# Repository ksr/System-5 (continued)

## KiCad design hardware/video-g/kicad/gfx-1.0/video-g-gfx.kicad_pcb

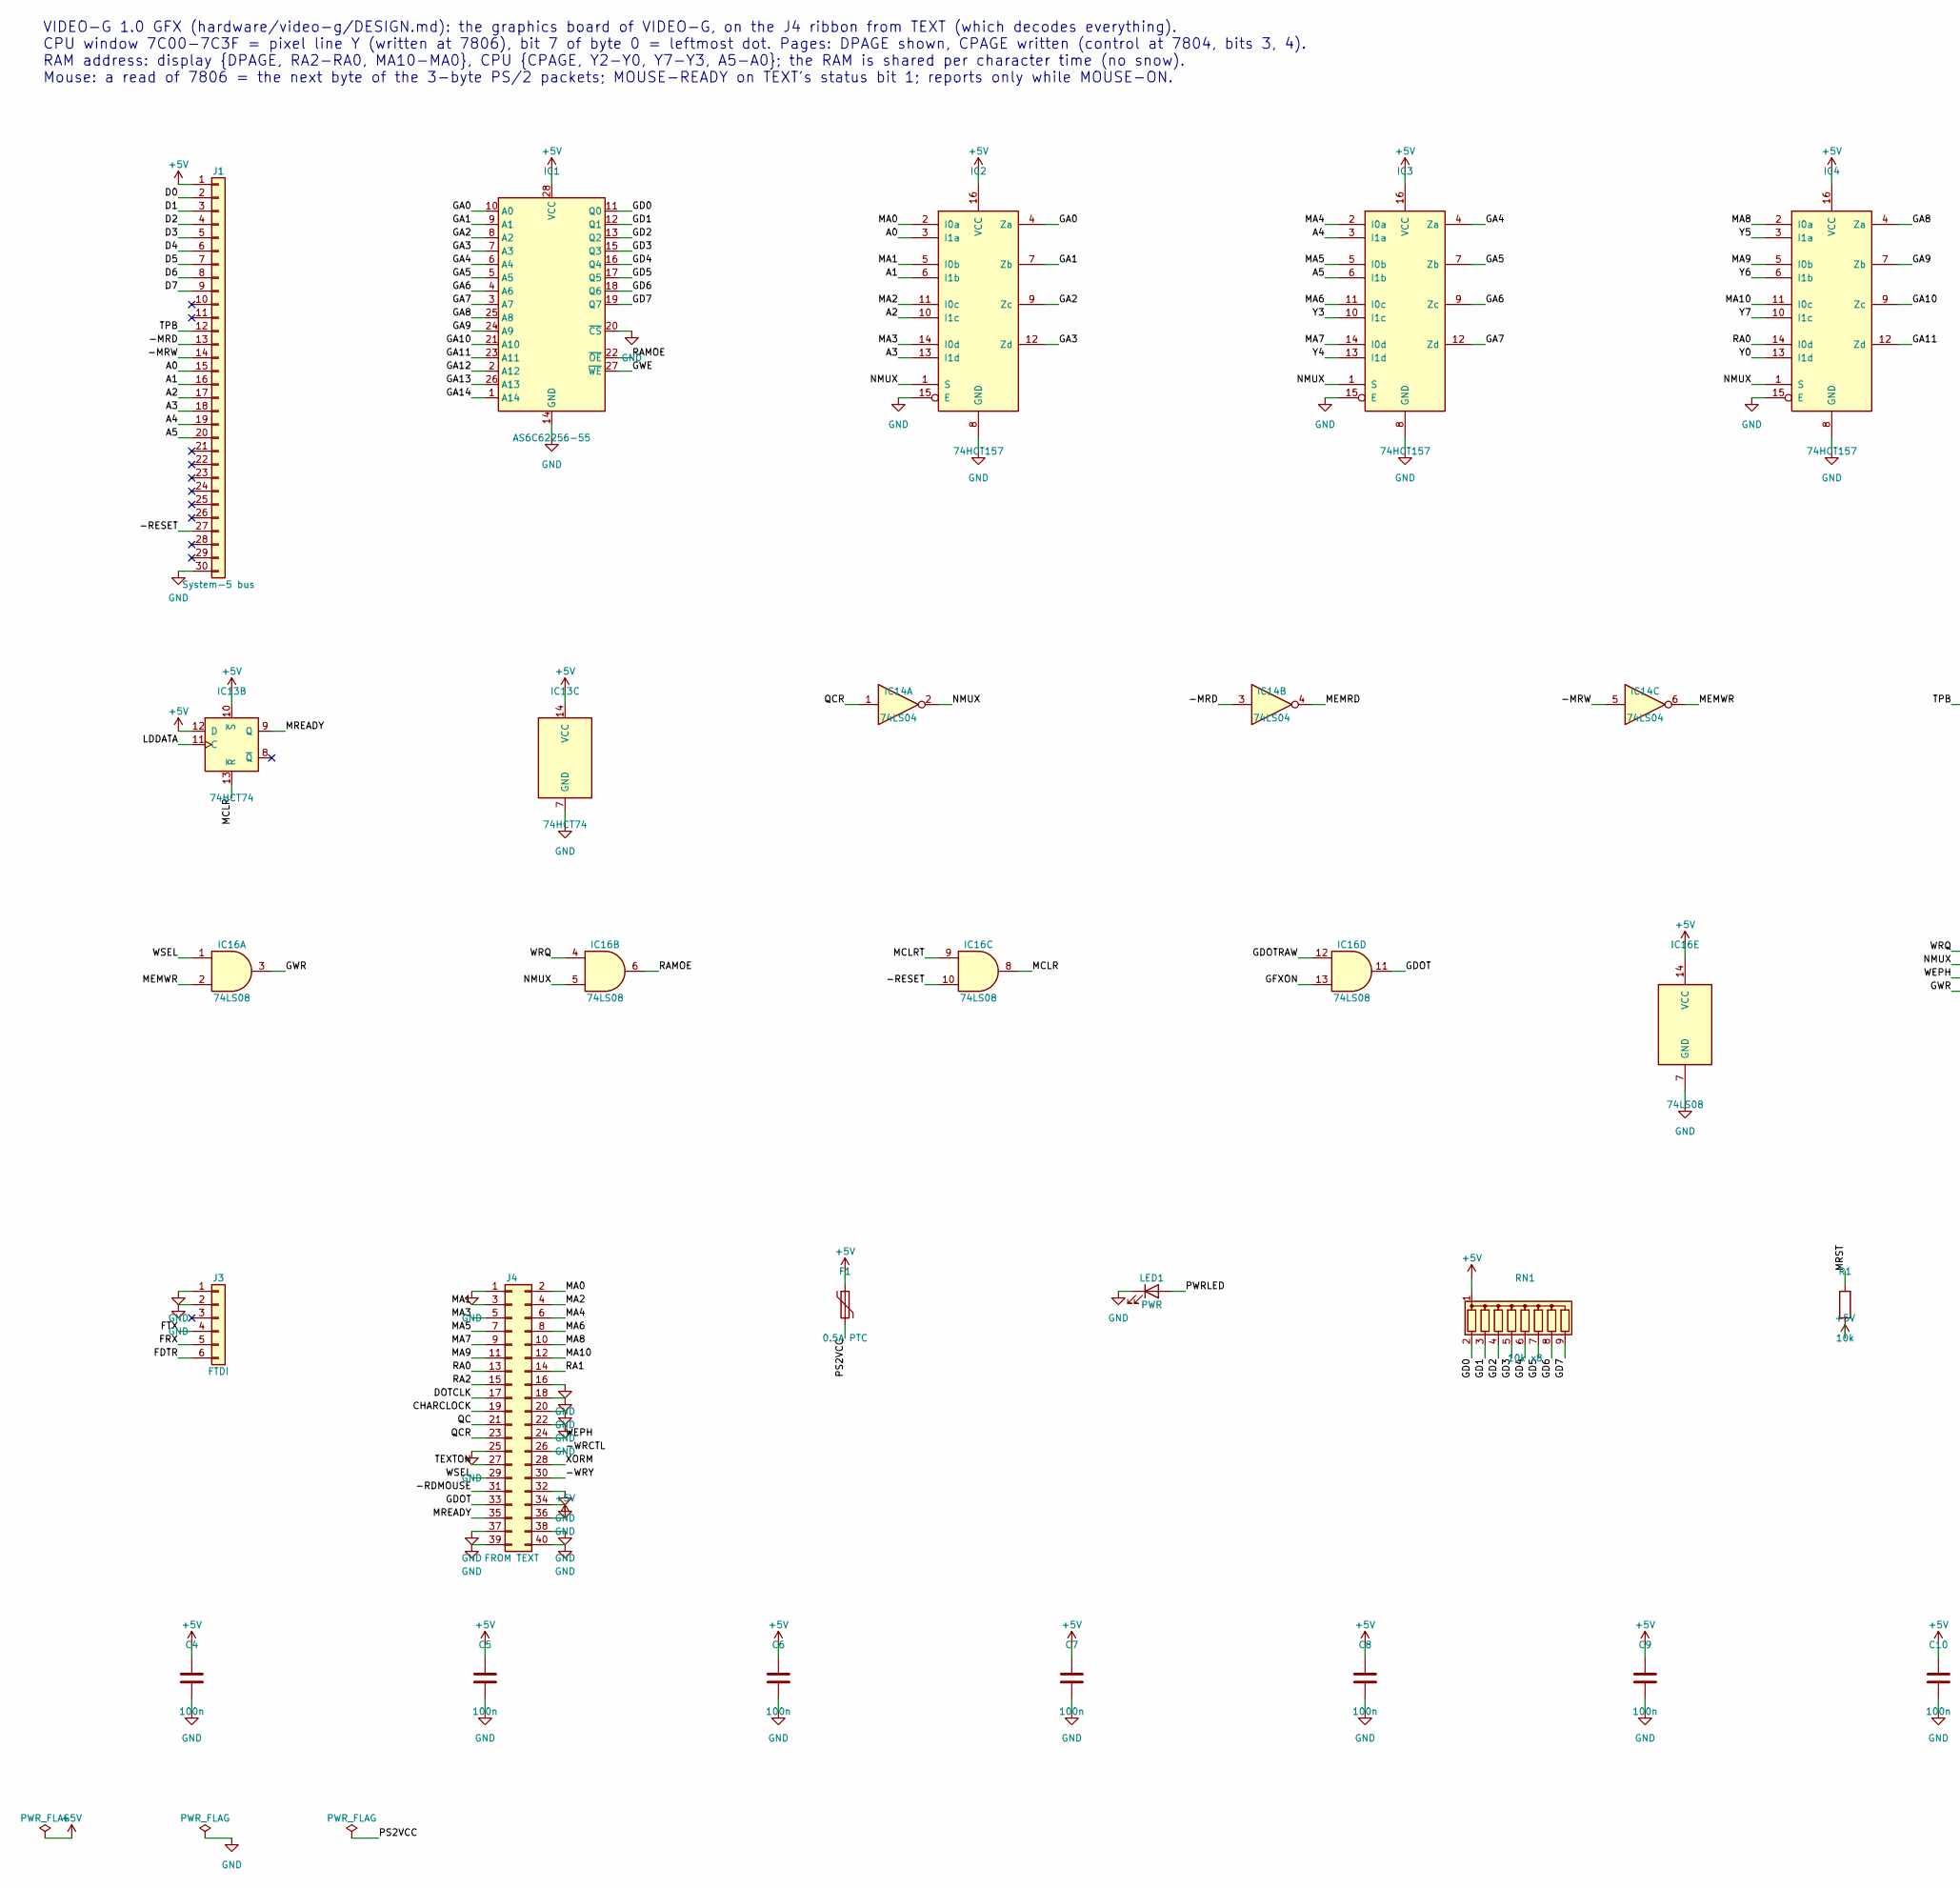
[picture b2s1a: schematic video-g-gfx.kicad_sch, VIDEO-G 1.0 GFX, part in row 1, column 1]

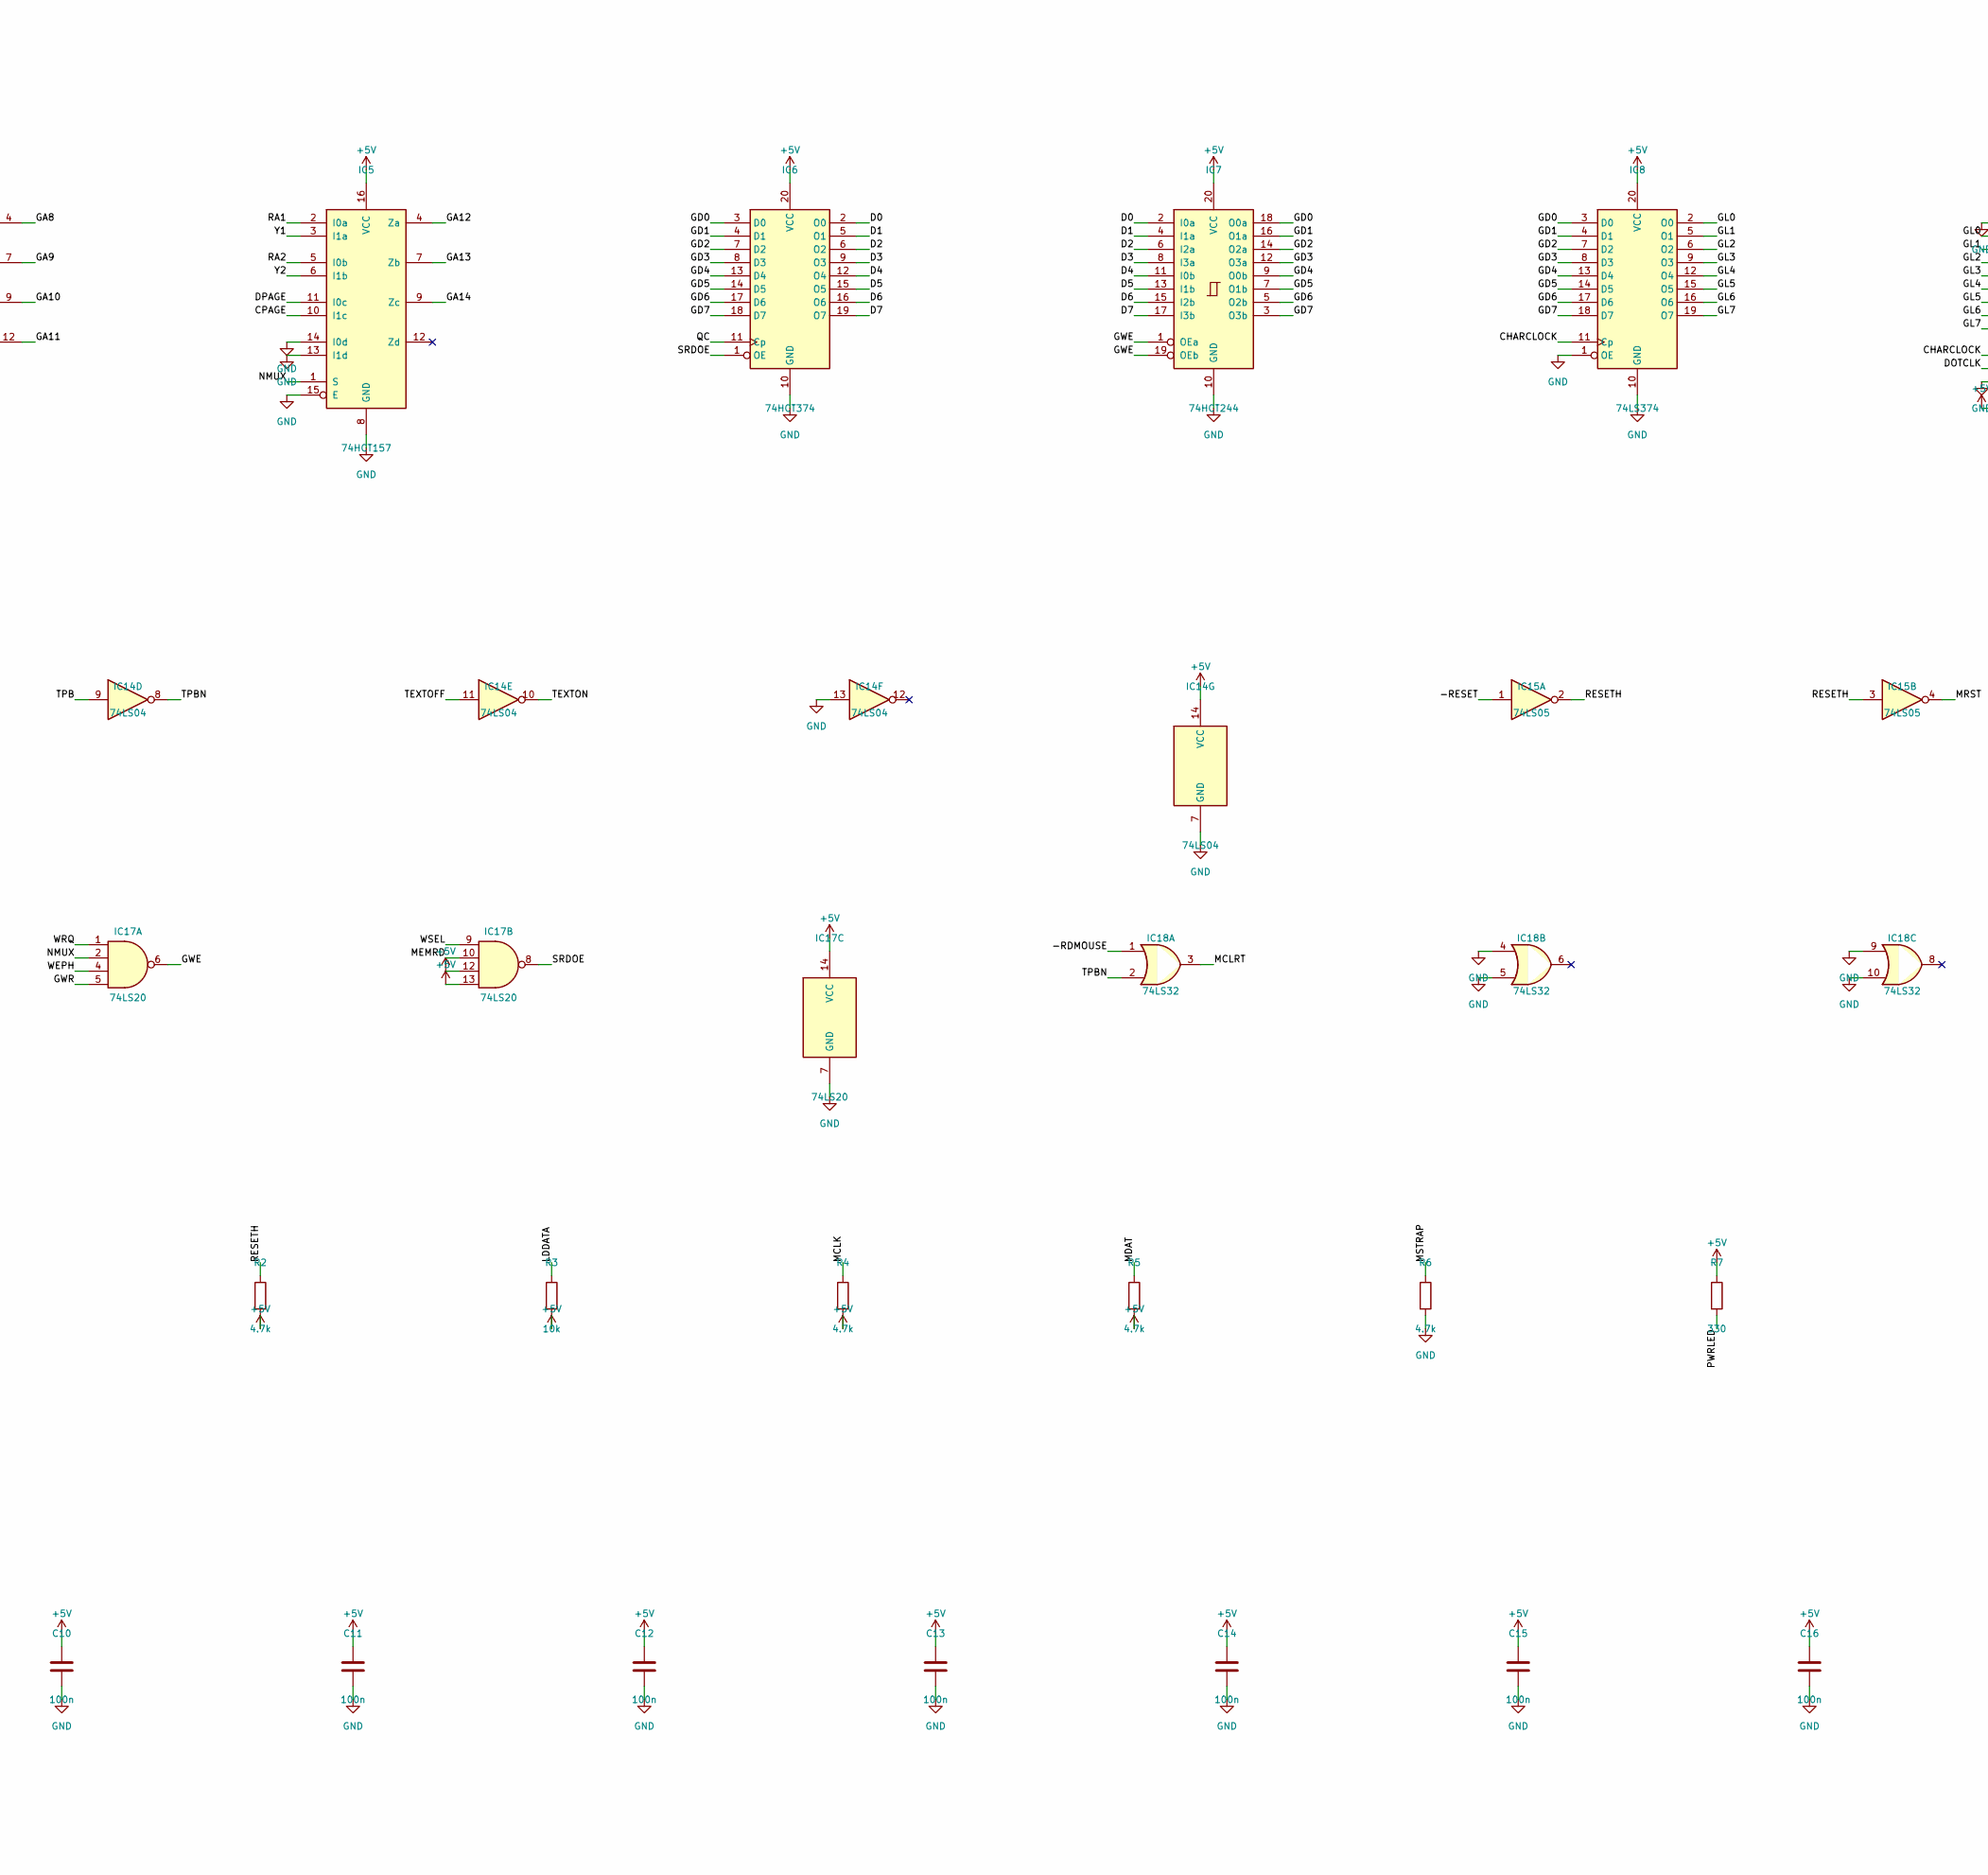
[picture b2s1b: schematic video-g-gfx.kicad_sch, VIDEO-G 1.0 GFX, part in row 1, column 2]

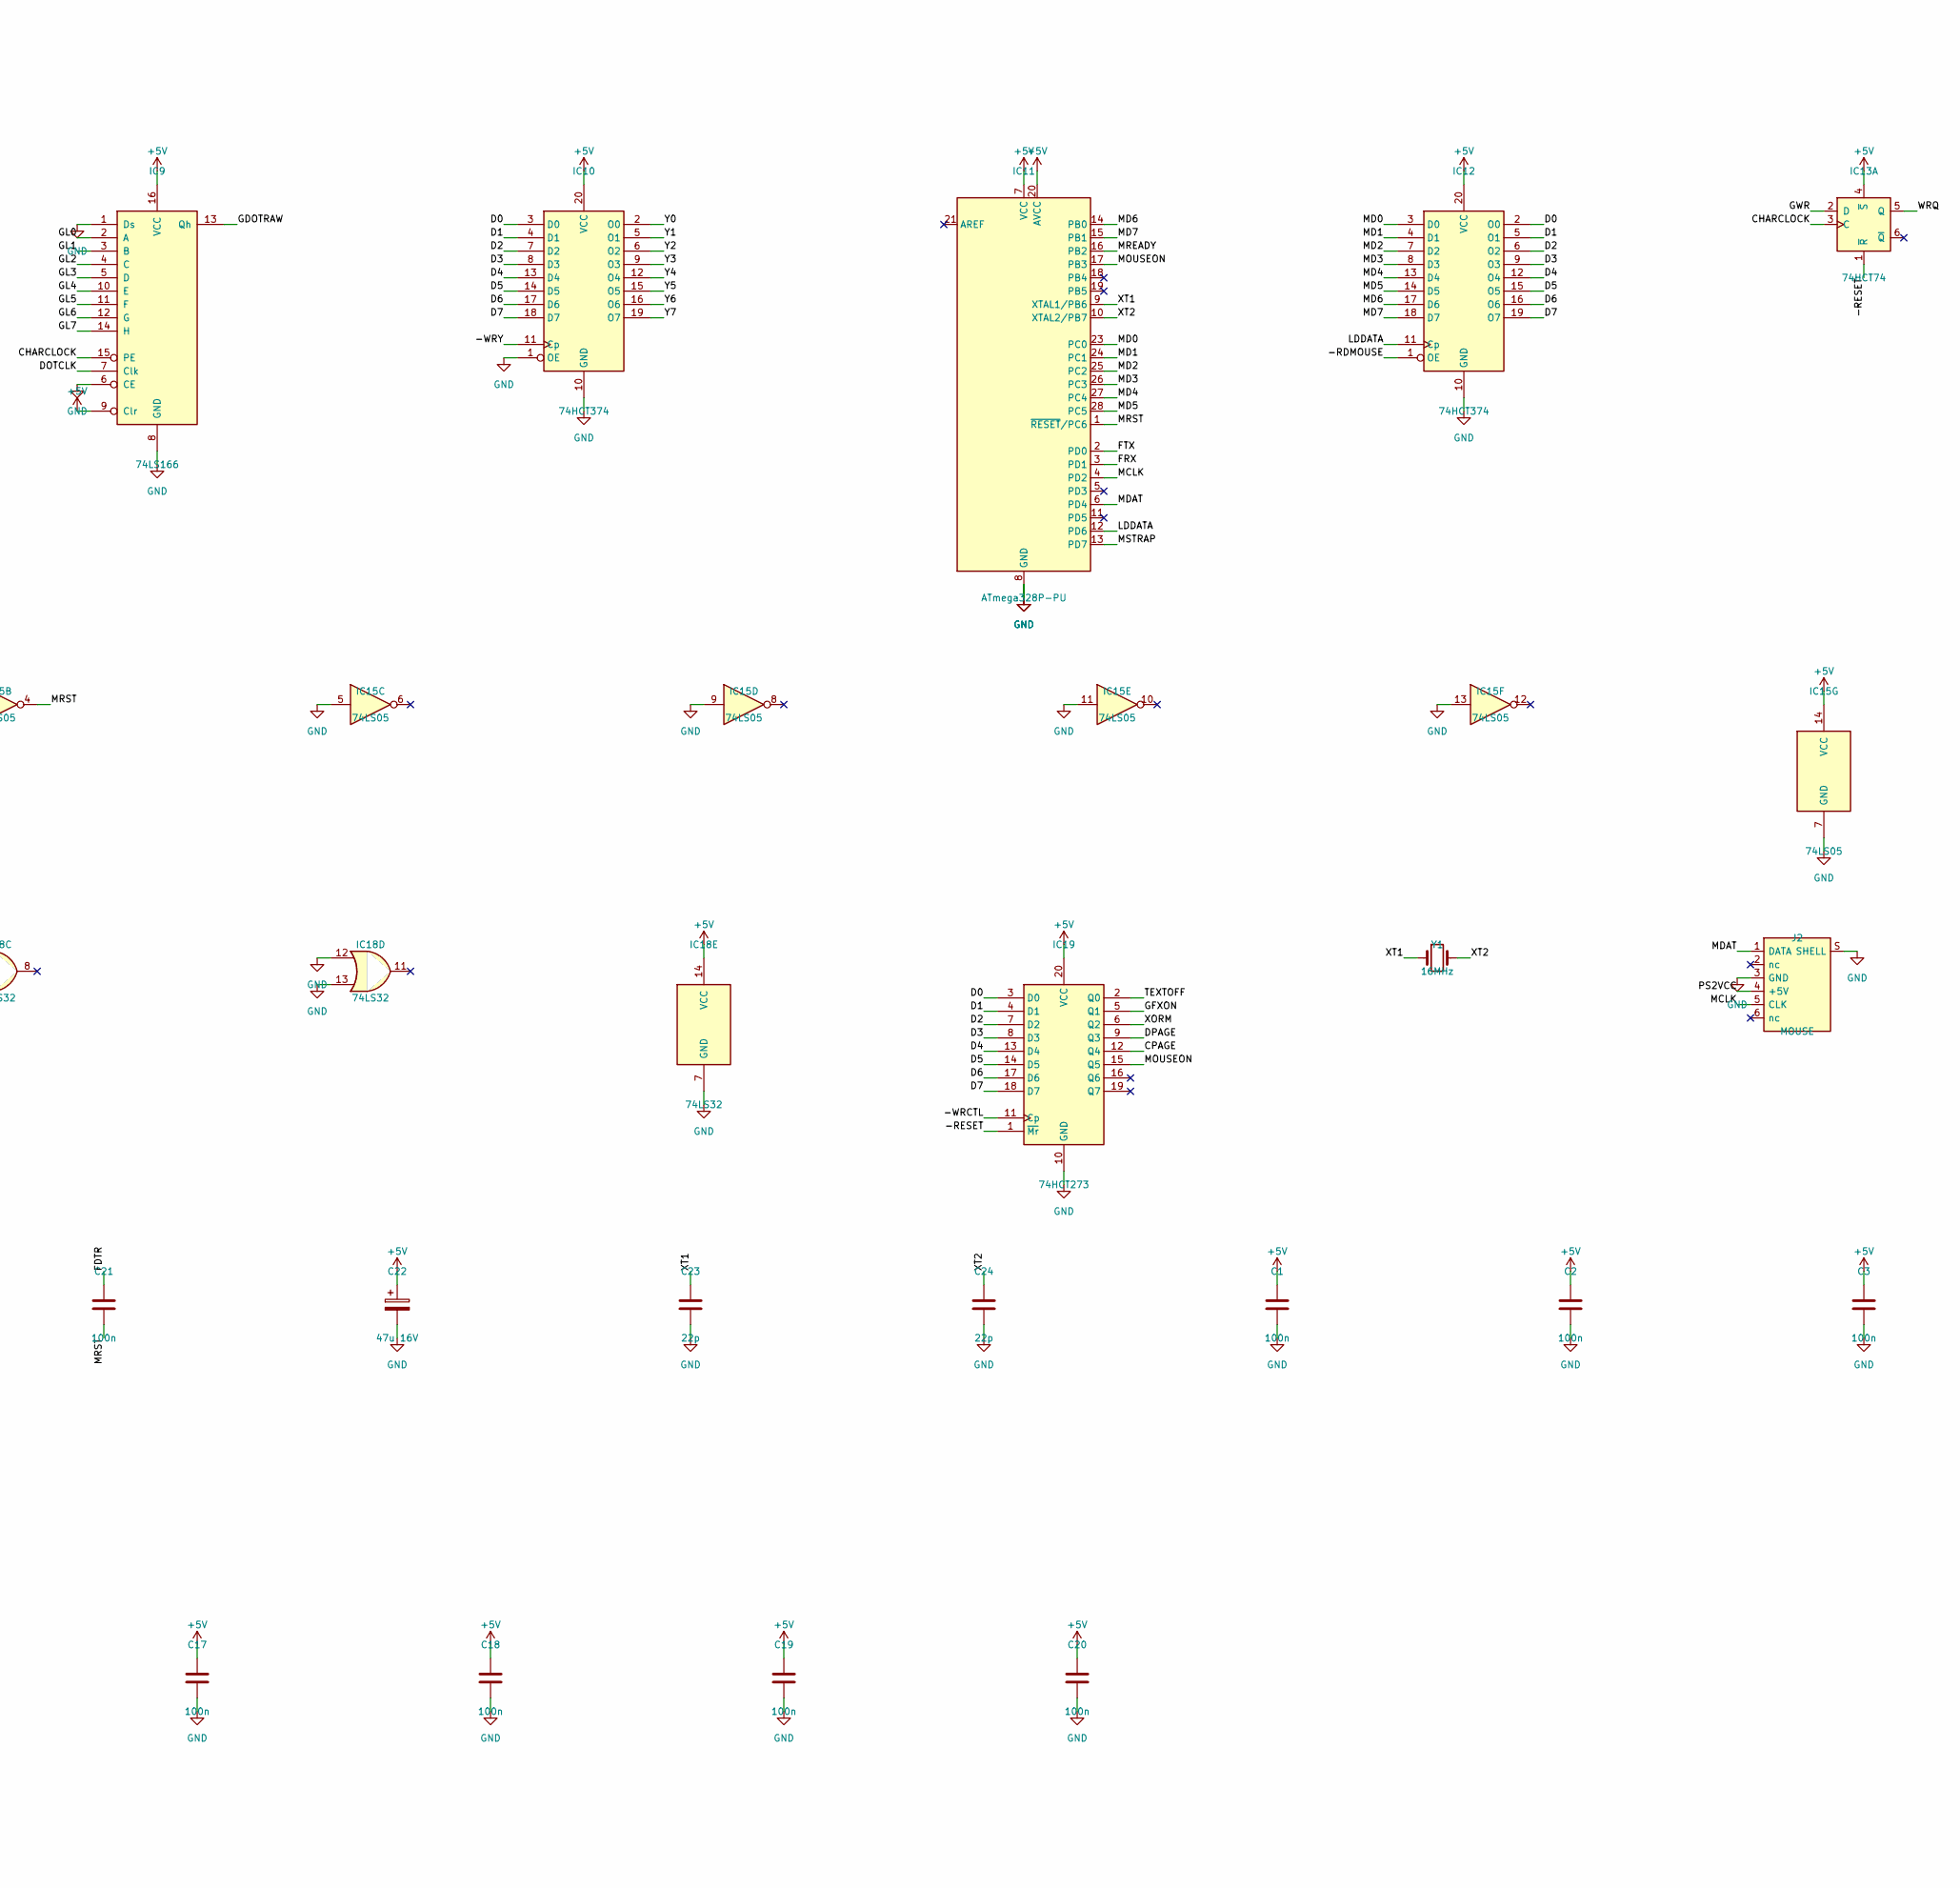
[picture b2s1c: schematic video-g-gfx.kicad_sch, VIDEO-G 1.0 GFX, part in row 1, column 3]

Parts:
C1, C2, C3, C4, C5, C6, C7, C8, C9, C10, C11, C12, C13, C14, C15, C16, C17, C18, C19, C20, C21: 100n; C025-050X050
C22: 47u 16V; CP_Radial_D6.3mm_P2.50mm
C23, C24: 22p; C025-050X050
F1: 0.5A PTC; Fuse_Bourns_MF-RHT050
IC1: AS6C62256-55; DIP-28_W15.24mm_Socket
IC2, IC3, IC4, IC5: 74HCT157; DIP-16_W7.62mm_Socket
IC6, IC10, IC12: 74HCT374; DIP-20_W7.62mm_Socket
IC7: 74HCT244; DIP-20_W7.62mm_Socket
IC8: 74LS374; DIP-20_W7.62mm_Socket
IC9: 74LS166; DIP-16_W7.62mm_Socket
IC11: ATmega328P-PU; DIP-28_W7.62mm_Socket
IC13: 74HCT74; DIP-14_W7.62mm_Socket
IC14: 74LS04; DIP-14_W7.62mm_Socket
IC15: 74LS05; DIP-14_W7.62mm_Socket
IC16: 74LS08; DIP-14_W7.62mm_Socket
IC17: 74LS20; DIP-14_W7.62mm_Socket
IC18: 74LS32; DIP-14_W7.62mm_Socket
IC19: 74HCT273; DIP-20_W7.62mm_Socket
J1: System-5 bus; C30
J2: MOUSE; MiniDIN6_MD-60SM
J3: FTDI; PinHeader_1x06_P2.54mm_Vertical
J4: FROM TEXT; IDC-Header_2x20_P2.54mm_Vertical
LED1: PWR; LED_D5.0mm
R1, R3: 10k; R_Axial_DIN0207_L6.3mm_D2.5mm_P2.54mm_Vertical
R2, R4, R5, R6: 4.7k; R_Axial_DIN0207_L6.3mm_D2.5mm_P2.54mm_Vertical
R7: 330; R_Axial_DIN0207_L6.3mm_D2.5mm_P2.54mm_Vertical
RN1: 10k x8; R_Array_SIP9
Y1: 16MHz; Crystal_HC49-U_Vertical

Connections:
+5V: C1.1, C2.1, C3.1, C4.1, C5.1, C6.1, C7.1, C8.1, C9.1, C10.1, C11.1, C12.1, C13.1, C14.1, C15.1, C16.1, C17.1, C18.1, C19.1, C20.1, C22.1, F1.1, IC1.28 (VCC), IC2.16 (VCC), IC3.16 (VCC), IC4.16 (VCC), IC5.16 (VCC), IC6.20 (VCC), IC7.20 (VCC), IC8.20 (VCC), IC9.9 (Clr), IC9.16 (VCC), IC10.20 (VCC), IC11.7 (VCC), IC11.20 (AVCC), IC12.20 (VCC), IC13.4 (~S), IC13.10 (~S), IC13.12 (D), IC13.14 (VCC), IC14.14 (VCC), IC15.14 (VCC), IC16.14 (VCC), IC17.12, IC17.13, IC17.14 (VCC), IC18.14 (VCC), IC19.20 (VCC), J1.1, J4.36, R1.2, R2.2, R3.2, R4.2, R5.2, R7.1, RN1.1 (common)
/-MRD: IC14.3, J1.13
/-MRW: IC14.5, J1.14
/-RDMOUSE: IC12.1 (OE), IC18.1, J4.31
/-RESET: IC13.1 (~R), IC15.1, IC16.10, IC19.1 (~Mr), J1.27
/-WRCTL: IC19.11 (Cp), J4.26
/-WRY: IC10.11 (Cp), J4.30
/A0: IC2.3 (I1a), J1.15
/A1: IC2.6 (I1b), J1.16
/A2: IC2.10 (I1c), J1.17
/A3: IC2.13 (I1d), J1.18
/A4: IC3.3 (I1a), J1.19
/A5: IC3.6 (I1b), J1.20
/CHARCLOCK: IC8.11 (Cp), IC9.15 (PE), IC13.3 (C), J4.19
/CPAGE: IC5.10 (I1c), IC19.12 (Q4)
/D0: IC6.2 (O0), IC7.2 (I0a), IC10.3 (D0), IC12.2 (O0), IC19.3 (D0), J1.2
/D1: IC6.5 (O1), IC7.4 (I1a), IC10.4 (D1), IC12.5 (O1), IC19.4 (D1), J1.3
/D2: IC6.6 (O2), IC7.6 (I2a), IC10.7 (D2), IC12.6 (O2), IC19.7 (D2), J1.4
/D3: IC6.9 (O3), IC7.8 (I3a), IC10.8 (D3), IC12.9 (O3), IC19.8 (D3), J1.5
/D4: IC6.12 (O4), IC7.11 (I0b), IC10.13 (D4), IC12.12 (O4), IC19.13 (D4), J1.6
/D5: IC6.15 (O5), IC7.13 (I1b), IC10.14 (D5), IC12.15 (O5), IC19.14 (D5), J1.7
/D6: IC6.16 (O6), IC7.15 (I2b), IC10.17 (D6), IC12.16 (O6), IC19.17 (D6), J1.8
/D7: IC6.19 (O7), IC7.17 (I3b), IC10.18 (D7), IC12.19 (O7), IC19.18 (D7), J1.9
/DOTCLK: IC9.7 (Clk), J4.17
/DPAGE: IC5.11 (I0c), IC19.9 (Q3)
/FDTR: C21.1, J3.6
/FRX: IC11.3 (PD1), J3.5
/FTX: IC11.2 (PD0), J3.4
/GA0: IC1.10 (A0), IC2.4 (Za)
/GA1: IC1.9 (A1), IC2.7 (Zb)
/GA2: IC1.8 (A2), IC2.9 (Zc)
/GA3: IC1.7 (A3), IC2.12 (Zd)
/GA4: IC1.6 (A4), IC3.4 (Za)
/GA5: IC1.5 (A5), IC3.7 (Zb)
/GA6: IC1.4 (A6), IC3.9 (Zc)
/GA7: IC1.3 (A7), IC3.12 (Zd)
/GA8: IC1.25 (A8), IC4.4 (Za)
/GA9: IC1.24 (A9), IC4.7 (Zb)
/GA10: IC1.21 (A10), IC4.9 (Zc)
/GA11: IC1.23 (A11), IC4.12 (Zd)
/GA12: IC1.2 (A12), IC5.4 (Za)
/GA13: IC1.26 (A13), IC5.7 (Zb)
/GA14: IC1.1 (A14), IC5.9 (Zc)
/GD0: IC1.11 (Q0), IC6.3 (D0), IC7.18 (O0a), IC8.3 (D0), RN1.2 (R1)
/GD1: IC1.12 (Q1), IC6.4 (D1), IC7.16 (O1a), IC8.4 (D1), RN1.3 (R2)
/GD2: IC1.13 (Q2), IC6.7 (D2), IC7.14 (O2a), IC8.7 (D2), RN1.4 (R3)
/GD3: IC1.15 (Q3), IC6.8 (D3), IC7.12 (O3a), IC8.8 (D3), RN1.5 (R4)
/GD4: IC1.16 (Q4), IC6.13 (D4), IC7.9 (O0b), IC8.13 (D4), RN1.6 (R5)
/GD5: IC1.17 (Q5), IC6.14 (D5), IC7.7 (O1b), IC8.14 (D5), RN1.7 (R6)
/GD6: IC1.18 (Q6), IC6.17 (D6), IC7.5 (O2b), IC8.17 (D6), RN1.8 (R7)
/GD7: IC1.19 (Q7), IC6.18 (D7), IC7.3 (O3b), IC8.18 (D7), RN1.9 (R8)
/GDOT: IC16.11, J4.33
/GDOTRAW: IC9.13 (Qh), IC16.12
/GFXON: IC16.13, IC19.5 (Q1)
/GL0: IC8.2 (O0), IC9.2 (A)
/GL1: IC8.5 (O1), IC9.3 (B)
/GL2: IC8.6 (O2), IC9.4 (C)
/GL3: IC8.9 (O3), IC9.5 (D)
/GL4: IC8.12 (O4), IC9.10 (E)
/GL5: IC8.15 (O5), IC9.11 (F)
/GL6: IC8.16 (O6), IC9.12 (G)
/GL7: IC8.19 (O7), IC9.14 (H)
/GWE: IC1.27 (~WE), IC7.1 (OEa), IC7.19 (OEb), IC17.6
/GWR: IC13.2 (D), IC16.3, IC17.5
/LDDATA: IC11.12 (PD6), IC12.11 (Cp), IC13.11 (C), R3.1
/MA0: IC2.2 (I0a), J4.2
/MA1: IC2.5 (I0b), J4.3
/MA2: IC2.11 (I0c), J4.4
/MA3: IC2.14 (I0d), J4.5
/MA4: IC3.2 (I0a), J4.6
/MA5: IC3.5 (I0b), J4.7
/MA6: IC3.11 (I0c), J4.8
/MA7: IC3.14 (I0d), J4.9
/MA8: IC4.2 (I0a), J4.10
/MA9: IC4.5 (I0b), J4.11
/MA10: IC4.11 (I0c), J4.12
/MCLK: IC11.4 (PD2), J2.5 (CLK), R4.1
/MCLR: IC13.13 (~R), IC16.8
/MCLRT: IC16.9, IC18.3
/MD0: IC11.23 (PC0), IC12.3 (D0)
/MD1: IC11.24 (PC1), IC12.4 (D1)
/MD2: IC11.25 (PC2), IC12.7 (D2)
/MD3: IC11.26 (PC3), IC12.8 (D3)
/MD4: IC11.27 (PC4), IC12.13 (D4)
/MD5: IC11.28 (PC5), IC12.14 (D5)
/MD6: IC11.14 (PB0), IC12.17 (D6)
/MD7: IC11.15 (PB1), IC12.18 (D7)
/MDAT: IC11.6 (PD4), J2.1 (DATA), R5.1
/MEMRD: IC14.4, IC17.10
/MEMWR: IC14.6, IC16.2
/MOUSEON: IC11.17 (PB3), IC19.15 (Q5)
/MREADY: IC11.16 (PB2), IC13.9 (Q), J4.35
/MRST: C21.2, IC11.1 (~RESET/PC6), IC15.4, R1.1
/MSTRAP: IC11.13 (PD7), R6.1
/NMUX: IC2.1 (S), IC3.1 (S), IC4.1 (S), IC5.1 (S), IC14.2, IC16.5, IC17.2
/PS2VCC: F1.2, J2.4 (+5V)
/PWRLED: LED1.2 (A), R7.2
/QC: IC6.11 (Cp), J4.21
/QCR: IC14.1, J4.23
/RA0: IC4.14 (I0d), J4.13
/RA1: IC5.2 (I0a), J4.14
/RA2: IC5.5 (I0b), J4.15
/RAMOE: IC1.22 (~OE), IC16.6
/RESETH: IC15.2, IC15.3, R2.1
/SRDOE: IC6.1 (OE), IC17.8
/TEXTOFF: IC14.11, IC19.2 (Q0)
/TEXTON: IC14.10, J4.27
/TPB: IC14.9, J1.12
/TPBN: IC14.8, IC18.2
/WEPH: IC17.4, J4.24
/WRQ: IC13.5 (Q), IC16.4, IC17.1
/WSEL: IC16.1, IC17.9, J4.29
/XORM: IC19.6 (Q2), J4.28
/XT1: C23.1, IC11.9 (XTAL1/PB6), Y1.1
/XT2: C24.1, IC11.10 (XTAL2/PB7), Y1.2
/Y0: IC4.13 (I1d), IC10.2 (O0)
/Y1: IC5.3 (I1a), IC10.5 (O1)
/Y2: IC5.6 (I1b), IC10.6 (O2)
/Y3: IC3.10 (I1c), IC10.9 (O3)
/Y4: IC3.13 (I1d), IC10.12 (O4)
/Y5: IC4.3 (I1a), IC10.15 (O5)
/Y6: IC4.6 (I1b), IC10.16 (O6)
/Y7: IC4.10 (I1c), IC10.19 (O7)
GND: C1.2, C2.2, C3.2, C4.2, C5.2, C6.2, C7.2, C8.2, C9.2, C10.2, C11.2, C12.2, C13.2, C14.2, C15.2, C16.2, C17.2, C18.2, C19.2, C20.2, C22.2, C23.2, C24.2, IC1.14 (GND), IC1.20 (~CS), IC2.8 (GND), IC2.15 (E), IC3.8 (GND), IC3.15 (E), IC4.8 (GND), IC4.15 (E), IC5.8 (GND), IC5.13 (I1d), IC5.14 (I0d), IC5.15 (E), IC6.10 (GND), IC7.10 (GND), IC8.1 (OE), IC8.10 (GND), IC9.1 (Ds), IC9.6 (CE), IC9.8 (GND), IC10.1 (OE), IC10.10 (GND), IC11.8 (GND), IC11.22 (GND), IC12.10 (GND), IC13.7 (GND), IC14.7 (GND), IC14.13, IC15.5, IC15.7 (GND), IC15.9, IC15.11, IC15.13, IC16.7 (GND), IC17.7 (GND), IC18.4, IC18.5, IC18.7 (GND), IC18.9, IC18.10, IC18.12, IC18.13, IC19.10 (GND), J1.30, J2.3 (GND), J2.S (SHELL), J3.1, J3.2, J4.1, J4.16, J4.18, J4.20, J4.22, J4.25, J4.32, J4.34, J4.37, J4.38, J4.39, J4.40, LED1.1 (K), R6.2

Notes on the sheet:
VIDEO-G 1.0 GFX (hardware/video-g/DESIGN.md): the graphics board of VIDEO-G, on the J4 ribbon from TEXT (which decodes everything).
CPU window 7C00-7C3F = pixel line Y (written at 7806), bit 7 of byte 0 = leftmost dot. Pages: DPAGE shown, CPAGE written (control at 7804, bits 3, 4).
RAM address: display {DPAGE, RA2-RA0, MA10-MA0}, CPU {CPAGE, Y2-Y0, Y7-Y3, A5-A0}; the RAM is shared per character time (no snow).
Mouse: a read of 7806 = the next byte of the 3-byte PS/2 packets; MOUSE-READY on TEXT's status bit 1; reports only while MOUSE-ON.

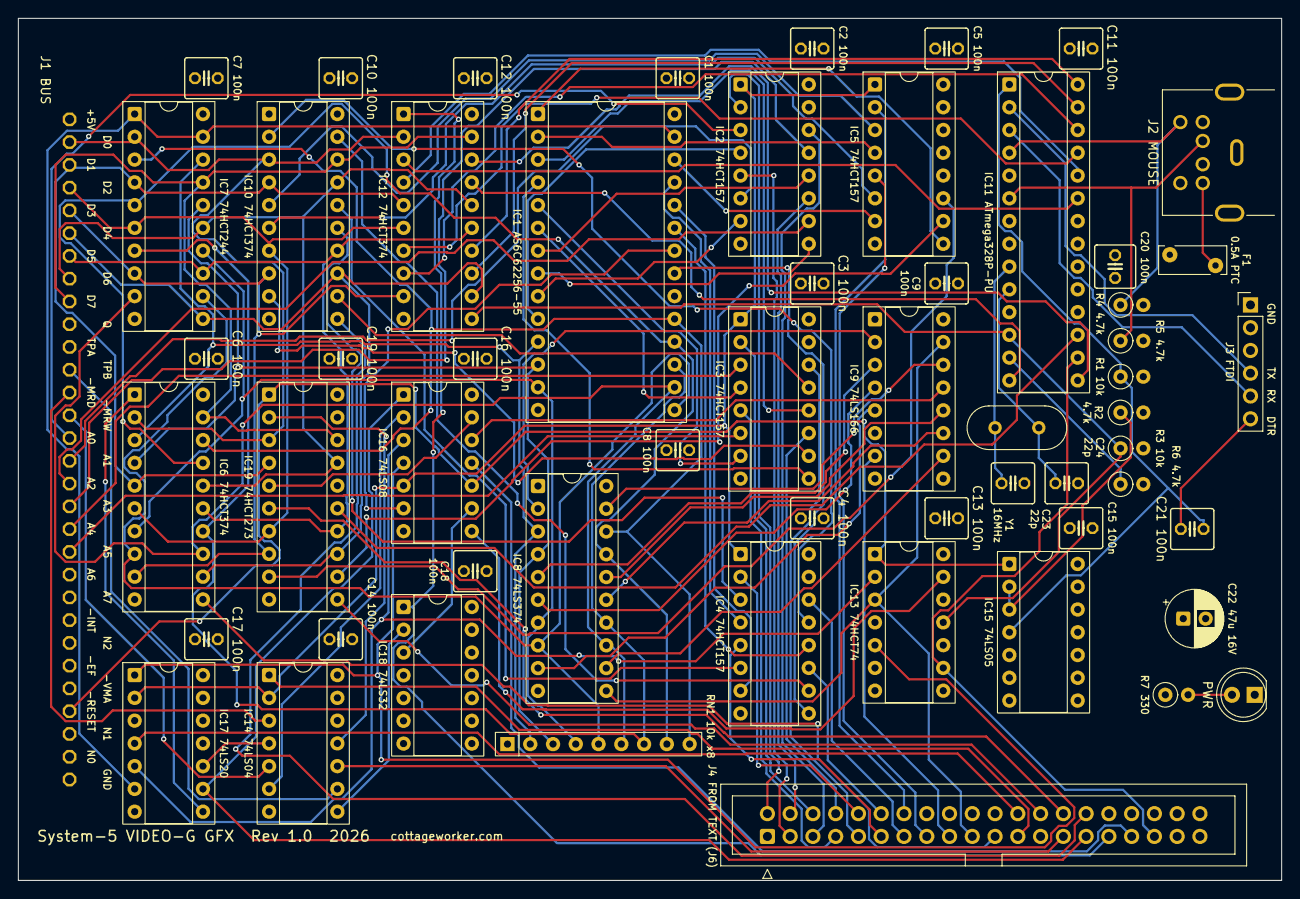
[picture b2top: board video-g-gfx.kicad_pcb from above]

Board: 4 copper layers, 140.9 x 96.2 mm, 58 parts (0 on the bottom side), 124 nets.

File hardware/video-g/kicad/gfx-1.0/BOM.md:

# VIDEO-G 1.0 GFX - bill of materials

Written by `hardware/video-g/kicad/common/bom.py` from `gen/netlist.py` (2026-11-17). Every IC goes in a socket.

| Qty | Value | Footprint | References | What to buy |
|---|---|---|---|---|
| 1 | AS6C62256-55 | DIP-28_W15.24mm_Socket | IC1 | AS6C62256-55PCN (Alliance, 55 ns, 600-mil DIP-28); not a 300-mil 'skinny' 62256 |
| 4 | 74HCT157 | DIP-16_W7.62mm_Socket | IC2, IC3, IC4, IC5 | 74HCT157 (CMOS inputs: no load on the 1802's address lines) |
| 3 | 74HCT374 | DIP-20_W7.62mm_Socket | IC6, IC10, IC12 |  |
| 1 | 74HCT244 | DIP-20_W7.62mm_Socket | IC7 |  |
| 1 | 74LS374 | DIP-20_W7.62mm_Socket | IC8 |  |
| 1 | 74LS166 | DIP-16_W7.62mm_Socket | IC9 |  |
| 1 | ATmega328P-PU | DIP-28_W7.62mm_Socket | IC11 | ATmega328P-PU with the Arduino Uno bootloader burned (ISP) before fitting |
| 1 | 74HCT74 | DIP-14_W7.62mm_Socket | IC13 |  |
| 1 | 74LS04 | DIP-14_W7.62mm_Socket | IC14 |  |
| 1 | 74LS05 | DIP-14_W7.62mm_Socket | IC15 |  |
| 1 | 74LS08 | DIP-14_W7.62mm_Socket | IC16 |  |
| 1 | 74LS20 | DIP-14_W7.62mm_Socket | IC17 |  |
| 1 | 74LS32 | DIP-14_W7.62mm_Socket | IC18 |  |
| 1 | 74HCT273 | DIP-20_W7.62mm_Socket | IC19 |  |
| 1 | 16MHz | Crystal_HC49-U_Vertical | Y1 | 16 MHz, HC-49/U, 18-20 pF load |
| 1 | System-5 bus | C30 | J1 | 1 x 30 right-angle pin header, 2.54 mm, single row (cut from a 1 x 40): its plastic body lies between the pads and the card edge, the pins out past the edge |
| 1 | MOUSE | MiniDIN6_MD-60SM | J2 | Same Sky (CUI Devices) MD-60SM, date code after 2022-03-03 |
| 1 | FTDI | PinHeader_1x06_P2.54mm_Vertical | J3 | 1 x 6 pin header, 2.54 mm (an FTDI cable programs the ATmega) |
| 1 | FROM TEXT | IDC-Header_2x20_P2.54mm_Vertical | J4 | 2 x 20 shrouded box header, 2.54 mm (the ribbon comes with the TEXT board's) |
| 1 | 0.5A PTC | Fuse_Bourns_MF-RHT050 | F1 | Bourns MF-RHT050 (0.5 A hold, radial) |
| 1 | PWR | LED_D5.0mm | LED1 |  |
| 1 | 10k x8 | R_Array_SIP9 | RN1 | 10k x8 BUSSED, pin 1 common, 9-pin SIP (e.g. Bourns 4609X-101-103LF) |
| 2 | 10k | R_Axial_DIN0207_L6.3mm_D2.5mm_P2.54mm_Vertical | R1, R3 | 1/4 W metal film, mounted standing |
| 4 | 4.7k | R_Axial_DIN0207_L6.3mm_D2.5mm_P2.54mm_Vertical | R2, R4, R5, R6 | 1/4 W metal film, mounted standing |
| 1 | 330 | R_Axial_DIN0207_L6.3mm_D2.5mm_P2.54mm_Vertical | R7 | 1/4 W metal film, mounted standing |
| 21 | 100n | C025-050X050 | C1, C2, C3, C4, C5, C6, C7, C8, C9, C10, C11, C12, C13, C14, C15, C16, C17, C18, C19, C20, C21 | ceramic X7R, 50 V, 0.1 in (2.54 mm) lead spacing |
| 1 | 47u 16V | CP_Radial_D6.3mm_P2.50mm | C22 | 47 uF electrolytic, 16 V or more, radial 6.3 mm, 2.5 mm pitch |
| 2 | 22p | C025-050X050 | C23, C24 | ceramic C0G (NP0), 50 V, 0.1 in lead spacing |

**IC sockets:** 6 x DIP-14, 300 mil, 5 x DIP-16, 300 mil, 6 x DIP-20, 300 mil, 1 x DIP-28, 600 mil, 1 x DIP-28, 300 mil

Totals: 19 ICs, 58 parts.
